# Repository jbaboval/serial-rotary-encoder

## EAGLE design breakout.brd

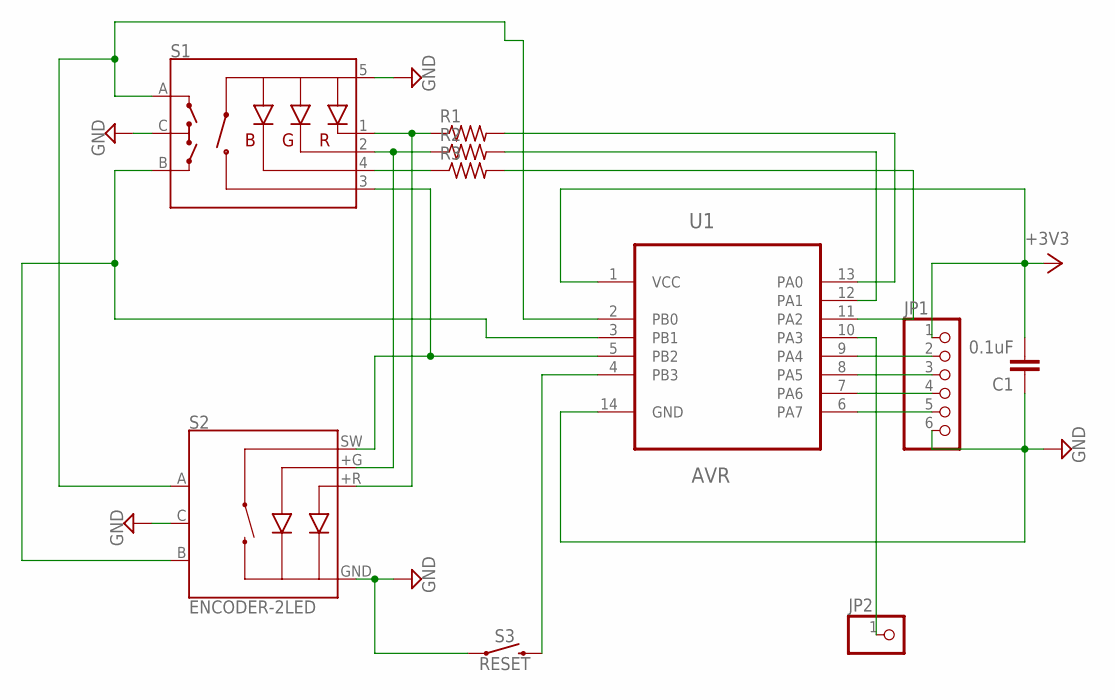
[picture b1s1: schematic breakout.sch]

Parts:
C1: 0.1uF; 0603
JP1: PINHD-1X6; 1X06
JP2: PINHD-1X1; 1X01
R1, R2, R3: R-US_M1206; M1206
S1: ENCODER-RGB-SWITCH; ENCODER_LED_3
S2: ENCODER-2LED; ENCODER_LED_2
S3: RESET; TACTILE_SWITCH_SMD_4.5MM
U1: AVR; SOIC127P600X175-14N

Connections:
+3V3: C1.2, JP1.1, U1.1 (VCC)
GND: C1.1, JP1.6, S1.5 (+), S1.C, S2.C, S2.GND (-), S3.2 (1), S3.3 (1), U1.14 (GND)
unnamed: JP1.2, U1.9 (PA4)
unnamed: JP1.3, U1.8 (PA5)
unnamed: JP1.4, U1.7 (PA6)
unnamed: JP1.5, U1.6 (PA7)
unnamed: S1.A, S2.A, U1.2 (PB0)
unnamed: S1.B, S2.B, U1.3 (PB1)
unnamed: S1.3 (SW), S2.SW, U1.5 (PB2)
unnamed: R1.1, S1.1 (-R), S2.+R
unnamed: R2.1, S1.2 (-G), S2.+G
unnamed: R3.1, S1.4 (-B)
unnamed: R1.2, U1.13 (PA0)
unnamed: R2.2, U1.12 (PA1)
unnamed: R3.2, U1.11 (PA2)
unnamed: S3.1 (2), S3.4 (2), U1.4 (PB3)
unnamed: JP2.1, U1.10 (PA3)

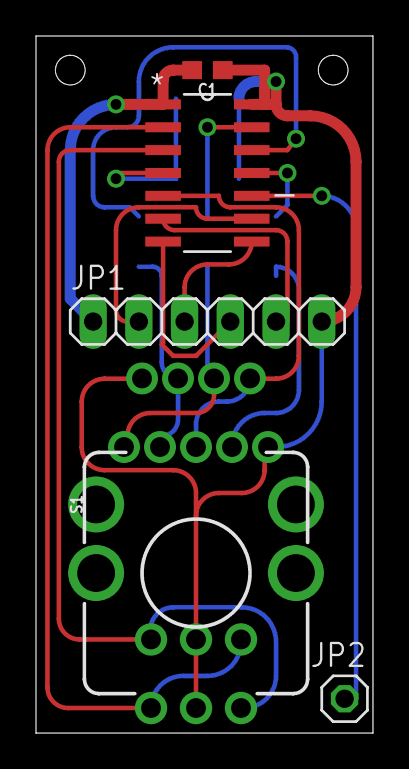
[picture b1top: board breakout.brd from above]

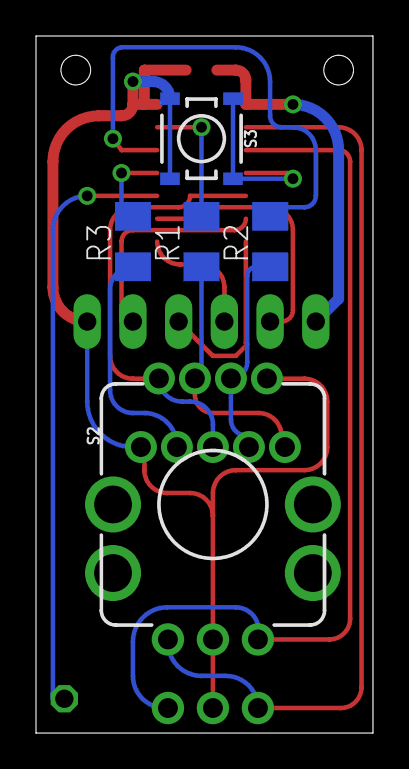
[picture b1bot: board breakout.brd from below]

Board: 2 copper layers, 18.7 x 38.7 mm, 10 parts (5 on the bottom side), 17 nets.

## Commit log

2017-04-22 Add Eagle project files
2017-04-22 Add Arduino .ino
2017-04-24 Debounce inputs independently Count half-cycles on quadrature input to support encoders with detents every half cycle Re-work ISR to access port register directly and use XOR - makes the code harder 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
2017-04-24 Clean up i2c protocol
2017-06-03 Use high-impedance mode toggle for intr pin to share interrupt line with multiple encoders
2019-03-24 Python Library for using encoder module on Raspberry Pi/CHIP/etc
2019-03-24 Change default from CHIP.io to RPi.GPIO Change interface to allow one instance per encoder board (GPIO/I2C objects become class attributes)

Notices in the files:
parts and their libraries:
SparkFun-Capacitors: Licensing: Creative Commons ShareAlike 4.0 International - https://creativecommons.org/licenses/by-sa/4.0
